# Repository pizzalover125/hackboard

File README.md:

# mini75
75 keys. ultra minimalism. game-changing

# BOM
* 75x Cherry MX Red 45g Linear Switches ($39.65 from MechanicalKeyboards.com)
* 107x YMDK 75 Keycaps + 120x Diodes ($35.73 from Amazon.com)
* 1x PCB ($30.41 from JLCPCB)
* 1x Orpheus Pico (FREE from closet)

**Total Price: 105.79**

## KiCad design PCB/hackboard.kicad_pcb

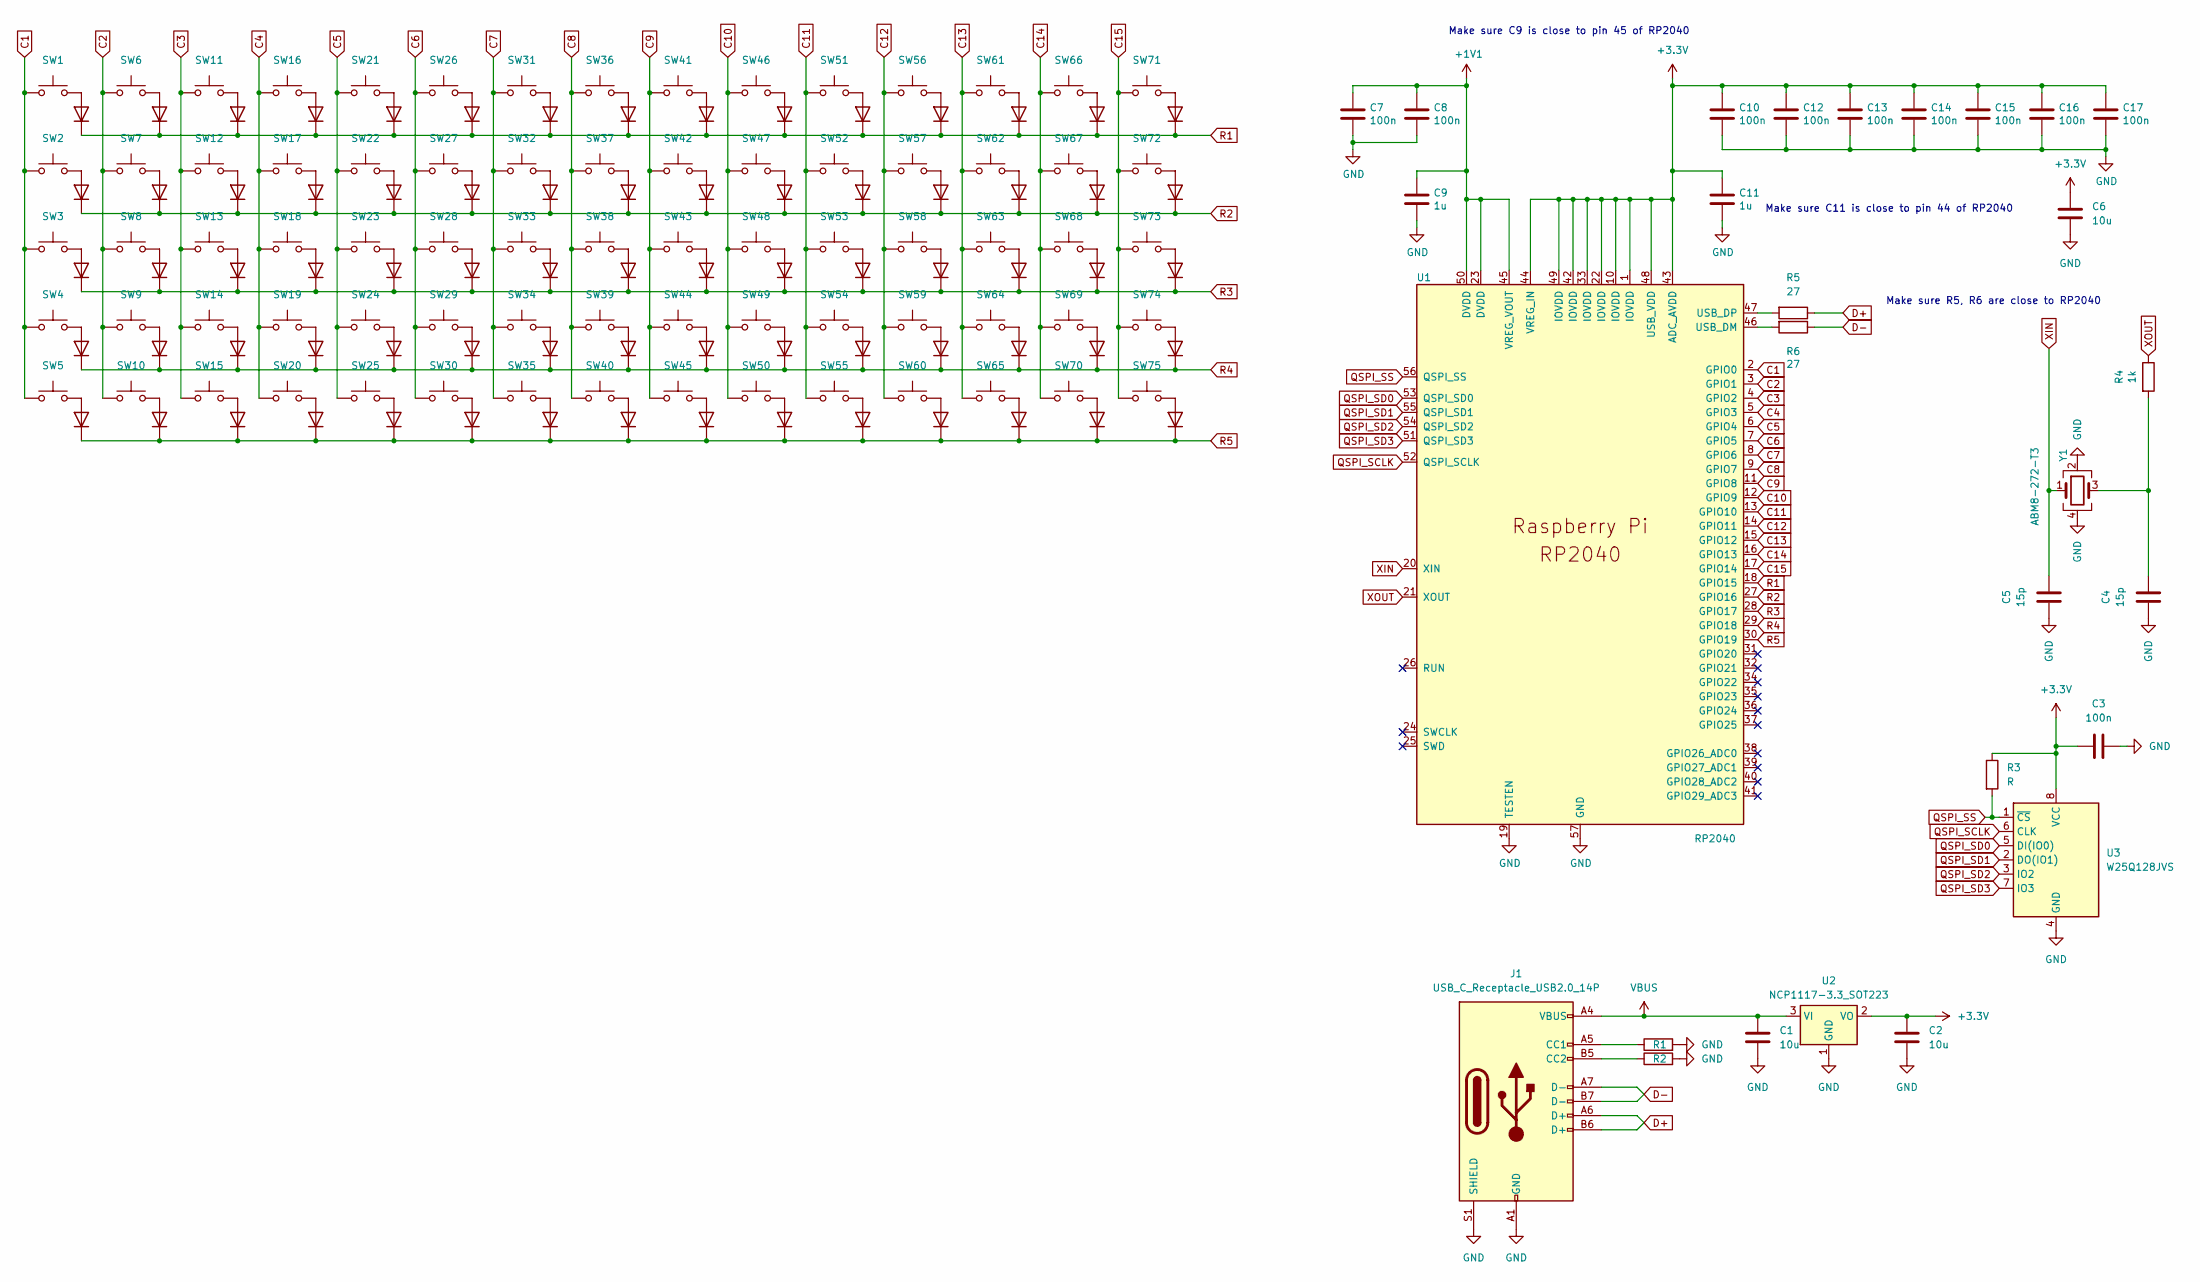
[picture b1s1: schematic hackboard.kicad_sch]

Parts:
C1, C2, C6: 10u; C_0805_2012Metric
C3, C7, C8, C10, C12, C13, C14, C15, C16, C17: 100n; C_0805_2012Metric
C4, C5: 15p; C_0805_2012Metric
C9, C11: 1u; C_0805_2012Metric
D1, D2, D3, D4, D5, D6, D7, D8, D9, D10, D11, D12, D13, D14, D15, D16, D17, D18, D19, D20, D21, D22, D23, D24, D25, D26, D27, D28, D29, D30, D31, D32, D33, D34, D35, D36, D37, D38, D39, D40, D41, D42, D43, D44, D45, D46, D47, D48, D49, D50, D51, D52, D53, D54, D55, D56, D57, D58, D59, D60, D61, D62, D63, D64, D65, D66, D67, D68, D69, D70, D71, D72, D73, D74, D75: D; D_DO-35_SOD27_P7.62mm_Horizontal
J1: USB_C_Receptacle_USB2.0_14P; USB_C_Receptacle_Amphenol_12401548E4-2A
R1, R2, R3: R; R_0805_2012Metric
R4: 1k; R_0805_2012Metric
R5, R6: 27; R_0805_2012Metric
SW1, SW2, SW3, SW4, SW5, SW6, SW7, SW8, SW9, SW10, SW11, SW12, SW13, SW14, SW15, SW16, SW17, SW18, SW19, SW20, SW21, SW22, SW23, SW24, SW25, SW26, SW27, SW28, SW29, SW30, SW31, SW32, SW33, SW34, SW35, SW36, SW37, SW38, SW39, SW40, SW41, SW42, SW43, SW44, SW45, SW46, SW47, SW48, SW49, SW50, SW51, SW52, SW53, SW54, SW55, SW56, SW57, SW58, SW59, SW60, SW61, SW62, SW63, SW64, SW65, SW66, SW67, SW68, SW69, SW70, SW71, SW72, SW73, SW74, SW75: SW_Push; SW_Cherry_MX_1.00u_PCB
U1: RP2040; QFN-56-1EP_7x7mm_P0.4mm_EP3.2x3.2mm
U2: NCP1117-3.3_SOT223; SOT230P700X180-4N
U3: W25Q128JVS; SOIC127P790X216-8N
Y1: ABM8-272-T3; Crystal_SMD_3225-4Pin_3.2x2.5mm

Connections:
+1V1: C7.1, C8.1, C9.1, U1.23 (DVDD), U1.45 (VREG_VOUT), U1.50 (DVDD)
+3.3V: C2.1, C3.1, C6.1, C10.1, C11.1, C12.1, C13.1, C14.1, C15.1, C16.1, C17.1, R3.1, U1.1 (IOVDD), U1.10 (IOVDD), U1.22 (IOVDD), U1.33 (IOVDD), U1.42 (IOVDD), U1.43 (ADC_AVDD), U1.44 (VREG_IN), U1.48 (USB_VDD), U1.49 (IOVDD), U2.2 (VO), U3.8 (VCC)
C1: SW1.1, SW2.1, SW3.1, SW4.1, SW5.1, U1.2 (GPIO0)
C2: SW6.1, SW7.1, SW8.1, SW9.1, SW10.1, U1.3 (GPIO1)
C3: SW11.1, SW12.1, SW13.1, SW14.1, SW15.1, U1.4 (GPIO2)
C4: SW16.1, SW17.1, SW18.1, SW19.1, SW20.1, U1.5 (GPIO3)
C5: SW21.1, SW22.1, SW23.1, SW24.1, SW25.1, U1.6 (GPIO4)
C6: SW26.1, SW27.1, SW28.1, SW29.1, SW30.1, U1.7 (GPIO5)
C7: SW31.1, SW32.1, SW33.1, SW34.1, SW35.1, U1.8 (GPIO6)
C8: SW36.1, SW37.1, SW38.1, SW39.1, SW40.1, U1.9 (GPIO7)
C9: SW41.1, SW42.1, SW43.1, SW44.1, SW45.1, U1.11 (GPIO8)
C10: SW46.1, SW47.1, SW48.1, SW49.1, SW50.1, U1.12 (GPIO9)
C11: SW51.1, SW52.1, SW53.1, SW54.1, SW55.1, U1.13 (GPIO10)
C12: SW56.1, SW57.1, SW58.1, SW59.1, SW60.1, U1.14 (GPIO11)
C13: SW61.1, SW62.1, SW63.1, SW64.1, SW65.1, U1.15 (GPIO12)
C14: SW66.1, SW67.1, SW68.1, SW69.1, SW70.1, U1.16 (GPIO13)
C15: SW71.1, SW72.1, SW73.1, SW74.1, SW75.1, U1.17 (GPIO14)
D+: J1.A6 (D+), J1.B6 (D+), R5.1
D-: J1.A7 (D-), J1.B7 (D-), R6.1
GND: C1.2, C2.2, C3.2, C4.1, C5.1, C6.2, C7.2, C8.2, C9.2, C10.2, C11.2, C12.2, C13.2, C14.2, C15.2, C16.2, C17.2, J1.A1 (GND), J1.A12 (GND), J1.B1 (GND), J1.B12 (GND), J1.S1 (SHIELD), R1.2, R2.2, U1.19 (TESTEN), U1.57 (GND), U2.1 (GND), U3.4 (GND), Y1.2, Y1.4
unnamed: C4.2, R4.2, Y1.3
unnamed: D1.2 (A), SW1.2
unnamed: D2.2 (A), SW2.2
unnamed: D3.2 (A), SW3.2
unnamed: D4.2 (A), SW4.2
unnamed: D5.2 (A), SW5.2
unnamed: D6.2 (A), SW6.2
unnamed: D7.2 (A), SW7.2
unnamed: D8.2 (A), SW8.2
unnamed: D9.2 (A), SW9.2
unnamed: D10.2 (A), SW10.2
unnamed: D11.2 (A), SW11.2
unnamed: D12.2 (A), SW12.2
unnamed: D13.2 (A), SW13.2
unnamed: D14.2 (A), SW14.2
unnamed: D15.2 (A), SW15.2
unnamed: D16.2 (A), SW16.2
unnamed: D17.2 (A), SW17.2
unnamed: D18.2 (A), SW18.2
unnamed: D19.2 (A), SW19.2
unnamed: D20.2 (A), SW20.2
unnamed: D21.2 (A), SW21.2
unnamed: D22.2 (A), SW22.2
unnamed: D23.2 (A), SW23.2
unnamed: D24.2 (A), SW24.2
unnamed: D25.2 (A), SW25.2
unnamed: D26.2 (A), SW26.2
unnamed: D27.2 (A), SW27.2
unnamed: D28.2 (A), SW28.2
unnamed: D29.2 (A), SW29.2
unnamed: D30.2 (A), SW30.2
unnamed: D31.2 (A), SW31.2
unnamed: D32.2 (A), SW32.2
unnamed: D33.2 (A), SW33.2
unnamed: D34.2 (A), SW34.2
unnamed: D35.2 (A), SW35.2
unnamed: D36.2 (A), SW36.2
unnamed: D37.2 (A), SW37.2
unnamed: D38.2 (A), SW38.2
unnamed: D39.2 (A), SW39.2
unnamed: D40.2 (A), SW40.2
unnamed: D41.2 (A), SW41.2
unnamed: D42.2 (A), SW42.2
unnamed: D43.2 (A), SW43.2
unnamed: D44.2 (A), SW44.2
unnamed: D45.2 (A), SW45.2
unnamed: D46.2 (A), SW46.2
unnamed: D47.2 (A), SW47.2
unnamed: D48.2 (A), SW48.2
unnamed: D49.2 (A), SW49.2
unnamed: D50.2 (A), SW50.2
unnamed: D51.2 (A), SW51.2
unnamed: D52.2 (A), SW52.2
unnamed: D53.2 (A), SW53.2
unnamed: D54.2 (A), SW54.2
unnamed: D55.2 (A), SW55.2
unnamed: D56.2 (A), SW56.2
unnamed: D57.2 (A), SW57.2
unnamed: D58.2 (A), SW58.2
unnamed: D59.2 (A), SW59.2
unnamed: D60.2 (A), SW60.2
unnamed: D61.2 (A), SW61.2
unnamed: D62.2 (A), SW62.2
unnamed: D63.2 (A), SW63.2
unnamed: D64.2 (A), SW64.2
unnamed: D65.2 (A), SW65.2
unnamed: D66.2 (A), SW66.2
unnamed: D67.2 (A), SW67.2
unnamed: D68.2 (A), SW68.2
unnamed: D69.2 (A), SW69.2
unnamed: D70.2 (A), SW70.2
unnamed: D71.2 (A), SW71.2
unnamed: D72.2 (A), SW72.2
unnamed: D73.2 (A), SW73.2
unnamed: D74.2 (A), SW74.2
unnamed: D75.2 (A), SW75.2
unnamed: J1.A5 (CC1), R1.1
unnamed: J1.B5 (CC2), R2.1
unnamed: R6.2, U1.46 (USB_DM)
unnamed: R5.2, U1.47 (USB_DP)
QSPI_SCLK: U1.52 (QSPI_SCLK), U3.6 (CLK)
QSPI_SD0: U1.53 (QSPI_SD0), U3.5 (DI(IO0))
QSPI_SD1: U1.55 (QSPI_SD1), U3.2 (DO(IO1))
QSPI_SD2: U1.54 (QSPI_SD2), U3.3 (IO2)
QSPI_SD3: U1.51 (QSPI_SD3), U3.7 (IO3)
QSPI_SS: R3.2, U1.56 (QSPI_SS), U3.1 (~CS)
R1: D1.1 (K), D6.1 (K), D11.1 (K), D16.1 (K), D21.1 (K), D26.1 (K), D31.1 (K), D36.1 (K), D41.1 (K), D46.1 (K), D51.1 (K), D56.1 (K), D61.1 (K), D66.1 (K), D71.1 (K), U1.18 (GPIO15)
R2: D2.1 (K), D7.1 (K), D12.1 (K), D17.1 (K), D22.1 (K), D27.1 (K), D32.1 (K), D37.1 (K), D42.1 (K), D47.1 (K), D52.1 (K), D57.1 (K), D62.1 (K), D67.1 (K), D72.1 (K), U1.27 (GPIO16)
R3: D3.1 (K), D8.1 (K), D13.1 (K), D18.1 (K), D23.1 (K), D28.1 (K), D33.1 (K), D38.1 (K), D43.1 (K), D48.1 (K), D53.1 (K), D58.1 (K), D63.1 (K), D68.1 (K), D73.1 (K), U1.28 (GPIO17)
R4: D4.1 (K), D9.1 (K), D14.1 (K), D19.1 (K), D24.1 (K), D29.1 (K), D34.1 (K), D39.1 (K), D44.1 (K), D49.1 (K), D54.1 (K), D59.1 (K), D64.1 (K), D69.1 (K), D74.1 (K), U1.29 (GPIO18)
R5: D5.1 (K), D10.1 (K), D15.1 (K), D20.1 (K), D25.1 (K), D30.1 (K), D35.1 (K), D40.1 (K), D45.1 (K), D50.1 (K), D55.1 (K), D60.1 (K), D65.1 (K), D70.1 (K), D75.1 (K), U1.30 (GPIO19)
VBUS: C1.1, J1.A4 (VBUS), J1.A9 (VBUS), J1.B4 (VBUS), J1.B9 (VBUS), U2.3 (VI)
XIN: C5.2, U1.20 (XIN), Y1.1
XOUT: R4.1, U1.21 (XOUT)

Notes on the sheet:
Make sure C11 is close to pin 44 of RP2040
Make sure C9 is close to pin 45 of RP2040
Make sure R5, R6 are close to RP2040

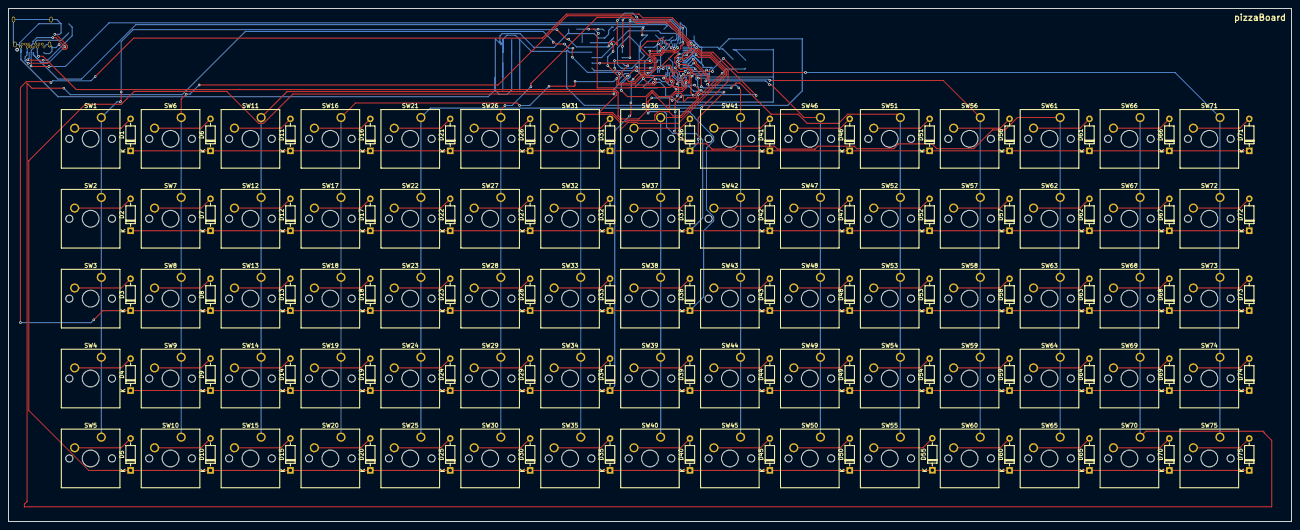
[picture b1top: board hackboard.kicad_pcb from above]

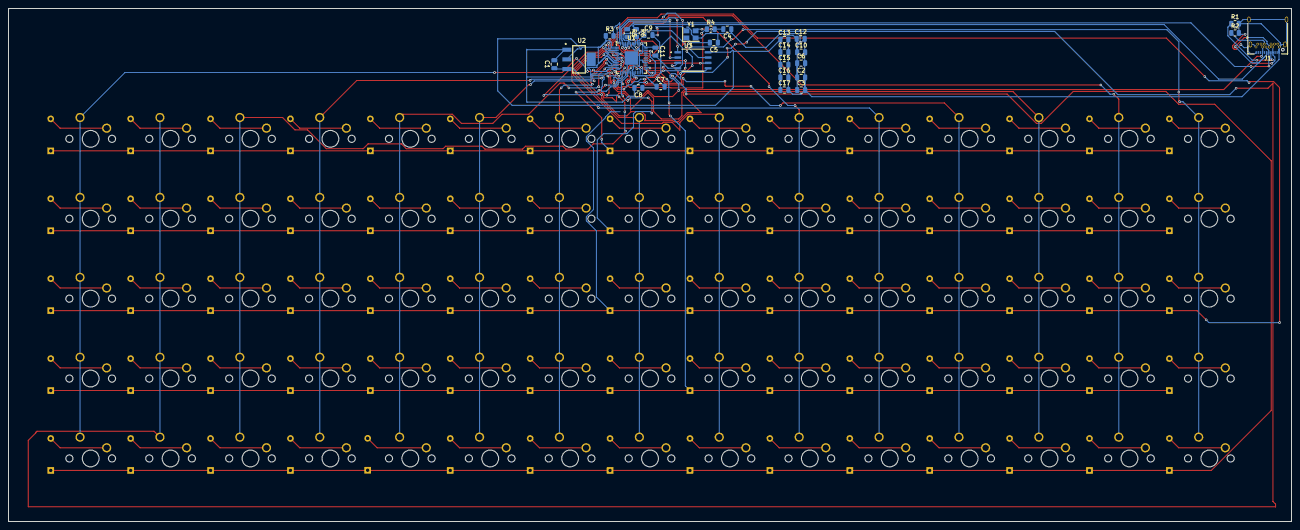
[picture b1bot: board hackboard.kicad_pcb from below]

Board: 2 copper layers, 305.9 x 122.3 mm, 178 parts (28 on the bottom side), 114 nets.
